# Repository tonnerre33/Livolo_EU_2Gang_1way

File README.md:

# Linovo_EU_2Gang_1way

## THIS NODE IS CURRENTLY IN DEVELOP
## YOU CAN SEE AND TEST THE DEV BRANCH AT YOUR OWN RISKS

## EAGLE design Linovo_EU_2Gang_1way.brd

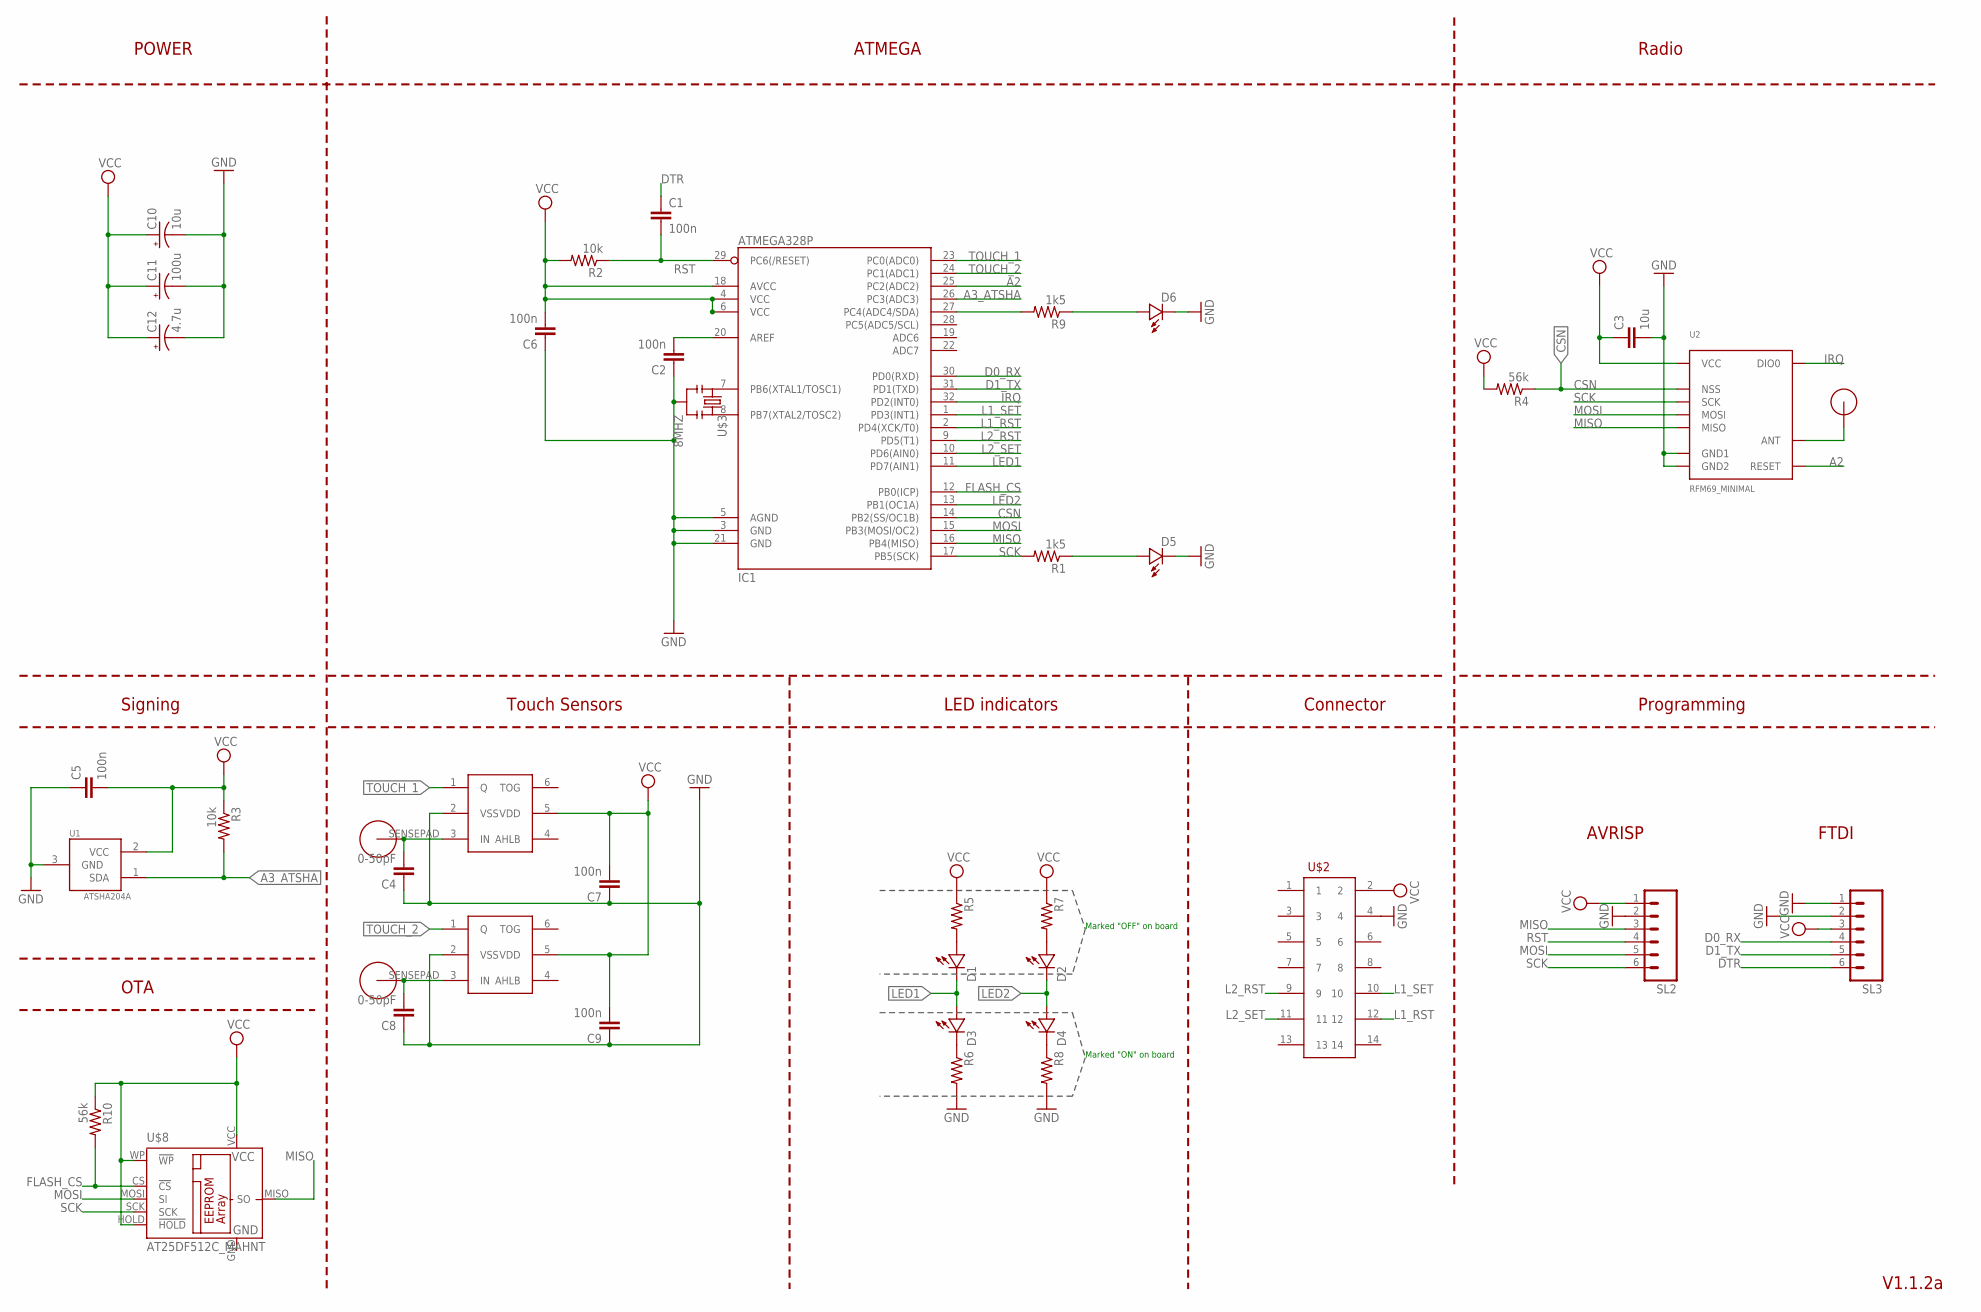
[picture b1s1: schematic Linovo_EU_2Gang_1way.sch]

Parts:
C1, C2, C6: 100n; 0402-CAP
C3: 10u; 0603-CAP
C4, C8: 0-50pF; 0603-CAP
C5, C7, C9: 100n; 0603-CAP
C10: 10u; EIA3216
C11: 100u; EIA3216
C12: 4.7u; EIA3216
D1, D2, D3, D4, D5, D6: LED0603; 0603-LED
IC1: ATMEGA328P; TQFP32-08
R1, R9: 1k5; 0603-RES
R2, R3: 10k; 0603-RES
R4, R10: 56k; 0603-RES
R5, R6, R7, R8: RESISTOR0603-RES; 0603-RES
SL2, SL3: M06SMD-1MM; 1X06-1MM
U1: ATSHA204A; SOT23-3
U2: RFM69_MINIMAL; RFM69CW_MINIMAL
U$1, U$5: SENSOR_PAD_ROUND; SENSING_PAD_ROUND
U$2: CONNECTOR_02_X_072MM_SPACING; CONNECTOR_02_X_07_2MM
U$3: 8MHZ; RESONATOR-SMD
U$4, U$6: TTP223-BA6; SOT-23-6
U$7: RFM12B_ANTENNA; RFM12B-ANTENNA
U$8: AT25DF512C_MAHNT

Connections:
A2: IC1.25 (PC2(ADC2)), U2.RESET
A3_ATSHA: IC1.26 (PC3(ADC3)), R3.2, U1.1 (SDA)
CSN: IC1.14 (PB2(SS/OC1B)), R4.1, U2.NSS
D0_RX: IC1.30 (PD0(RXD)), SL3.4
D1_TX: IC1.31 (PD1(TXD)), SL3.5
DTR: C1.1, SL3.6
FLASH_CS: IC1.12 (PB0(ICP)), R10.2, U$8.CS (!CS)
GND: C2.1, C3.2, C4.1, C5.1, C6.1, C7.1, C8.1, C9.1, C10.-, C11.-, C12.-, D5.MINUS, D6.MINUS, IC1.3 (GND), IC1.5 (AGND), IC1.21 (GND), R6.2, R8.2, SL2.2, SL3.1, SL3.2, U1.3 (GND), U2.GND (GND1), U2.GND2, U$2.4, U$3.2, U$4.2 (VSS), U$6.2 (VSS), U$8.GND
IRQ: IC1.32 (PD2(INT0)), U2.DIO0
L1_RST: IC1.2 (PD4(XCK/T0)), U$2.12
L1_SET: IC1.1 (PD3(INT1)), U$2.10
L2_RST: IC1.9 (PD5(T1)), U$2.9
L2_SET: IC1.10 (PD6(AIN0)), U$2.11
LED1: D1.MINUS, D3.PLUS, IC1.11 (PD7(AIN1))
LED2: D2.MINUS, D4.PLUS, IC1.13 (PB1(OC1A))
MISO: IC1.16 (PB4(MISO)), SL2.3, U2.MISO, U$8.MISO (SO)
MOSI: IC1.15 (PB3(MOSI/OC2)), SL2.5, U2.MOSI, U$8.MOSI (SI)
unnamed: D5.PLUS, R1.1
unnamed: IC1.7 (PB6(XTAL1/TOSC1)), U$3.1
unnamed: C4.2, U$1.SENSEPAD, U$4.3 (IN)
unnamed: C2.2, IC1.20 (AREF)
unnamed: D1.PLUS, R5.2
unnamed: D3.MINUS, R6.1
unnamed: D2.PLUS, R7.2
unnamed: IC1.8 (PB7(XTAL2/TOSC2)), U$3.3
unnamed: C8.2, U$5.SENSEPAD, U$6.3 (IN)
unnamed: D4.MINUS, R8.1
unnamed: D6.PLUS, R9.1
unnamed: IC1.27 (PC4(ADC4/SDA)), R9.2
unnamed: U2.ANT, U$7.P$1
RST: C1.2, IC1.29 (PC6(/RESET)), R2.1, SL2.4
SCK: IC1.17 (PB5(SCK)), R1.2, SL2.6, U2.SCK, U$8.SCK
TOUCH_1: IC1.23 (PC0(ADC0)), U$4.1 (Q)
TOUCH_2: IC1.24 (PC1(ADC1)), U$6.1 (Q)
VCC: C3.1, C5.2, C6.2, C7.2, C9.2, C10.+, C11.+, C12.+, IC1.4 (VCC), IC1.6 (VCC), IC1.18 (AVCC), R2.2, R3.1, R4.2, R5.1, R7.1, R10.1, SL2.1, SL3.3, U1.2 (VCC), U2.VDD (VCC), U$2.2, U$4.5 (VDD), U$6.5 (VDD), U$8.HOLD (!HOLD), U$8.VCC, U$8.WP (!WP)

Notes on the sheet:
Programming
FTDI
AVRISP
Radio
ATMEGA
POWER
Signing
V1.1.2a
Touch Sensors
Connector
LED indicators
Marked "OFF" on board
Marked "ON" on board
OTA

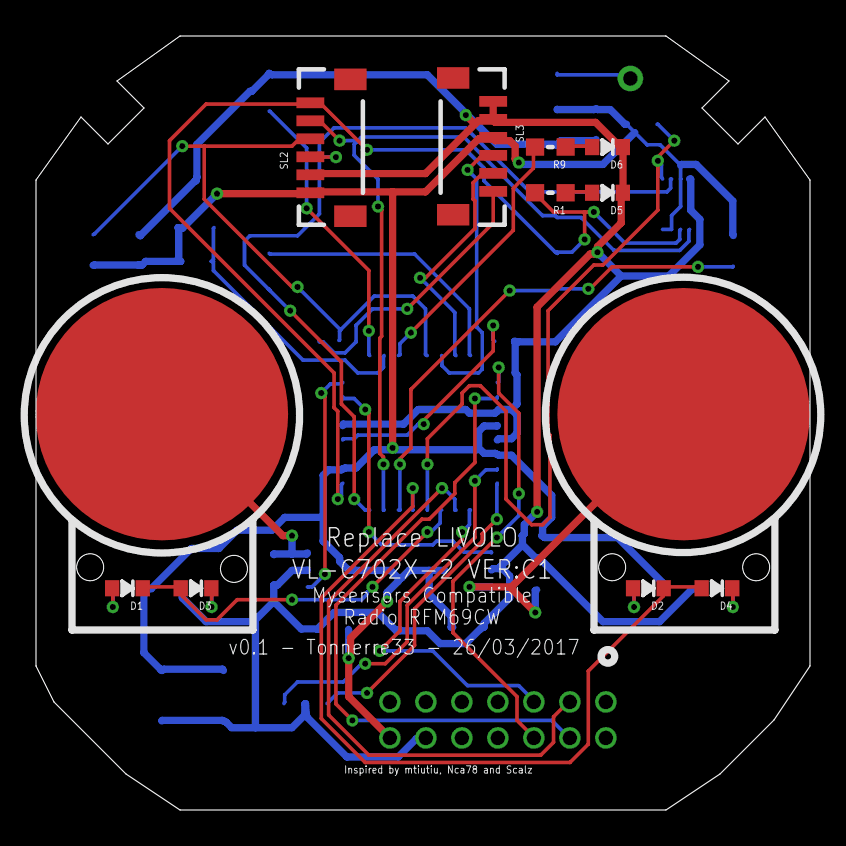
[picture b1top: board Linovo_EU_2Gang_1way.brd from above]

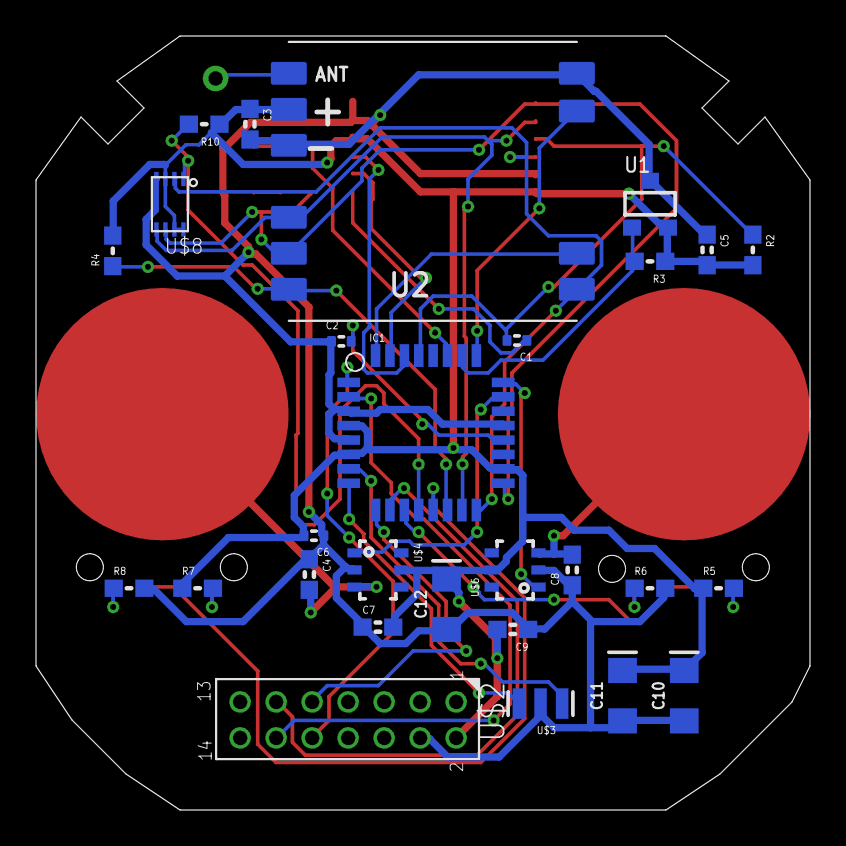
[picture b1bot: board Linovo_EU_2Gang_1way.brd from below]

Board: 2 copper layers, 43.0 x 43.0 mm, 41 parts (29 on the bottom side), 35 nets.

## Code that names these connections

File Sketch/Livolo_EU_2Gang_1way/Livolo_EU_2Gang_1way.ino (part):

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int ledPins[] = {7,A1}; //{LED BP LEFT, LED BP RIGHT}
byte buttonPins[] = {3,A0}; //{BP LEFT, BP RIGHT}
const uint8_t RELAY_CH_PINS[][2] = {
    {5, 4}, // channel 1 relay control pins(bistable relay - 2 coils) {L1_SET, L1_RST}
    {A3, A4}  // channel 2 relay control pins(bistable relay - 2 coils) {L2_SET, L2_RST}
};
#define MTSA_PIN 6
#define BUZZER_PIN A2
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
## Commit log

2017-03-26 First version of the PCB
2017-03-26 replace senspad & reroot
2017-03-26 Documentation Added
2017-03-26 Change value RFM69 capacitor
2017-04-01 Convert to Kicad
2017-04-01 Correct name project
2017-04-01 rootage
2017-04-01 Generate gerber files
2017-04-01 align sens pad
2017-04-01 update gerber
2017-04-01 move capacitor C11
2017-04-01 increase distance between pad and wire
2017-04-01 update gerber files
2017-04-01 saved schema but duno which modif
2017-04-02 move 14 pins connector
2017-04-02 cleanup schema
2017-04-02 Ceramic capacitor added in parrallel of Tantalum
2017-04-02 optimise position condensator senspad
2017-04-02 correct ERC errors
2017-04-02 optimise position C2
2017-04-02 capacitor added for OTA
2017-04-02 Text cleaning and Readme update
2017-04-02 Readme update
2017-04-08 power node by 12Vcc
2017-04-08 increase clearance netclass POWER from 8 to 10 mil
2017-04-08 cleaning
2017-04-08 replace bad footprint AT25DF512C
2017-04-08 Replace some capacitor 0402 -> 0603
2017-04-09 add documentation and BOM
2017-04-09 add ATMEGA328P doc
2017-04-09 update pdf schema
2017-04-15 Change FTDI wiring
2017-05-14 add doc
2017-06-12 Adding Sketch
2017-06-13 Change RFM69 by NRF24L01 cause crash
2017-06-13 Adding Symbols and footprint
2017-06-15 Sketch test
2017-06-16 version NRF24
2017-07-01 update sketch and adding TTP223 documentation
2017-07-29 change code
2017-07-29 replace TTP223 by MTCH105
2017-07-29 ajust silkscreen
2017-07-29 adding shunt for test with or without guard
2017-07-29 update version to v1.2 + pdf + gerber
2017-07-29 moving C6 for be closer of pin 4 and 5
2017-07-29 moving leds
2017-08-01 changes after mtiutiu advises! thx
2017-08-01 correct pin buzzer
2017-08-05 move sketch directory and correct radio text on pcb
2017-08-26 added instant mode
2017-08-26 move MTSA pin to a PWM pin of the ATMEGA
2017-08-26 remove resistor for guard
2017-10-04 optimize
2017-11-05 optimise code
2017-11-05 optimise code for settings by the air

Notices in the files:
parts and their libraries:
SparkFun-Capacitors: Licensing: Creative Commons ShareAlike 4.0 International - https://creativecommons.org/licenses/by-sa/4.0
